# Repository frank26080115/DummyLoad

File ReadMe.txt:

Full project details at:

http://www.frank-zhao.com/dummyload/

The circuit and PCB are designed in EAGLE 6.3.0

Compiling the bootloader requires LUFA to be installed (not included, get it yourself)

The firmware is compiled using Atmel Studio 6.1, with the accompanying AVRToolChain, which has AVR GCC 4.7.2

The box is a Hammond Mfg RL6115

===================================

Instructions:

Build the circuit, the PCB and schematic are both provided, so it's up to you to find the parts and get the PCB made and then solder everything.

The box needs to be drilled and cut. I used a drill, a dremel, and some files to get this done.

After the circuit is built, use an AVR programmer to flash the bootloader into the ATmega32U4

To activate the bootloader, hold down the rotary encoder push button, and plug in the USB cable.

The bootloader behaves as a USBasp, use AVRDUDE to bootload the firmware.

Adjust the LCD contrast using the potentiometer.

The virtual USB serial port requires a driver, see http://www.pjrc.com/teensy/td_download.html and look for "Windows Serial Driver"

When you first use the dummy load, you must connect it to a computer and open up the virtual serial port to do the calibration.

===================================

Calibration:

This is a measurement tool. Because of the various errors and tolerances of the components being used, it needs to be calibrated before being useful. Calibration is done against a known "calibrated" power supply, which must have adjustable voltage, with both voltage and current readouts.

Make sure the virtual serial port is open in a serial terminal.

Connect the red plug to the black plug.

Type the command "calivolts:0" and press enter, wait until you see "voltageOffset" being shown.

Connect the dummy load to the power supply that was discussed previously.

Set the precision power supply to exactly 5V

Type the command "calivolts:5" and press enter, wait until you see "voltageScale" being shown. If you are not using 5V, you can type in another voltage.

Type the command "caliamps:0" and press enter, wait until you see "currentOffset" being shown.

Rotate the knob until the power supply says it is supplying exactly 500mA, then type the command "caliamps:500" and press enter, wait until you see "currentDacScale" and "currentAdcScale" being shown.

If you cannot get exactly 500mA, you can actually type in any number equal to the current being drawn.

All calibration values are stored in EEPROM. There are default values if the values are invalid or missing in the EEPROM.

====================================

Other Serial Terminal Commands

All of these commands are lower case, case sensitive, and must end with one of \r \n or \0, you can hit enter to do this.

"start" will start the logging output in comma separated value format

"stop" will stop the logging output

"single" will output only one line of measurement

"set:123.45" will set the current to 123.45 mA, you can specify any number you want

"set16:12345" will send 12345 to the DAC, this is only used for testing

"info" will report the calibration values

There are a few more internal testing commands that you do not need to know, see the source code if you are interested.

I recommend using RealTerm because it has a simple interface for logging to a file.

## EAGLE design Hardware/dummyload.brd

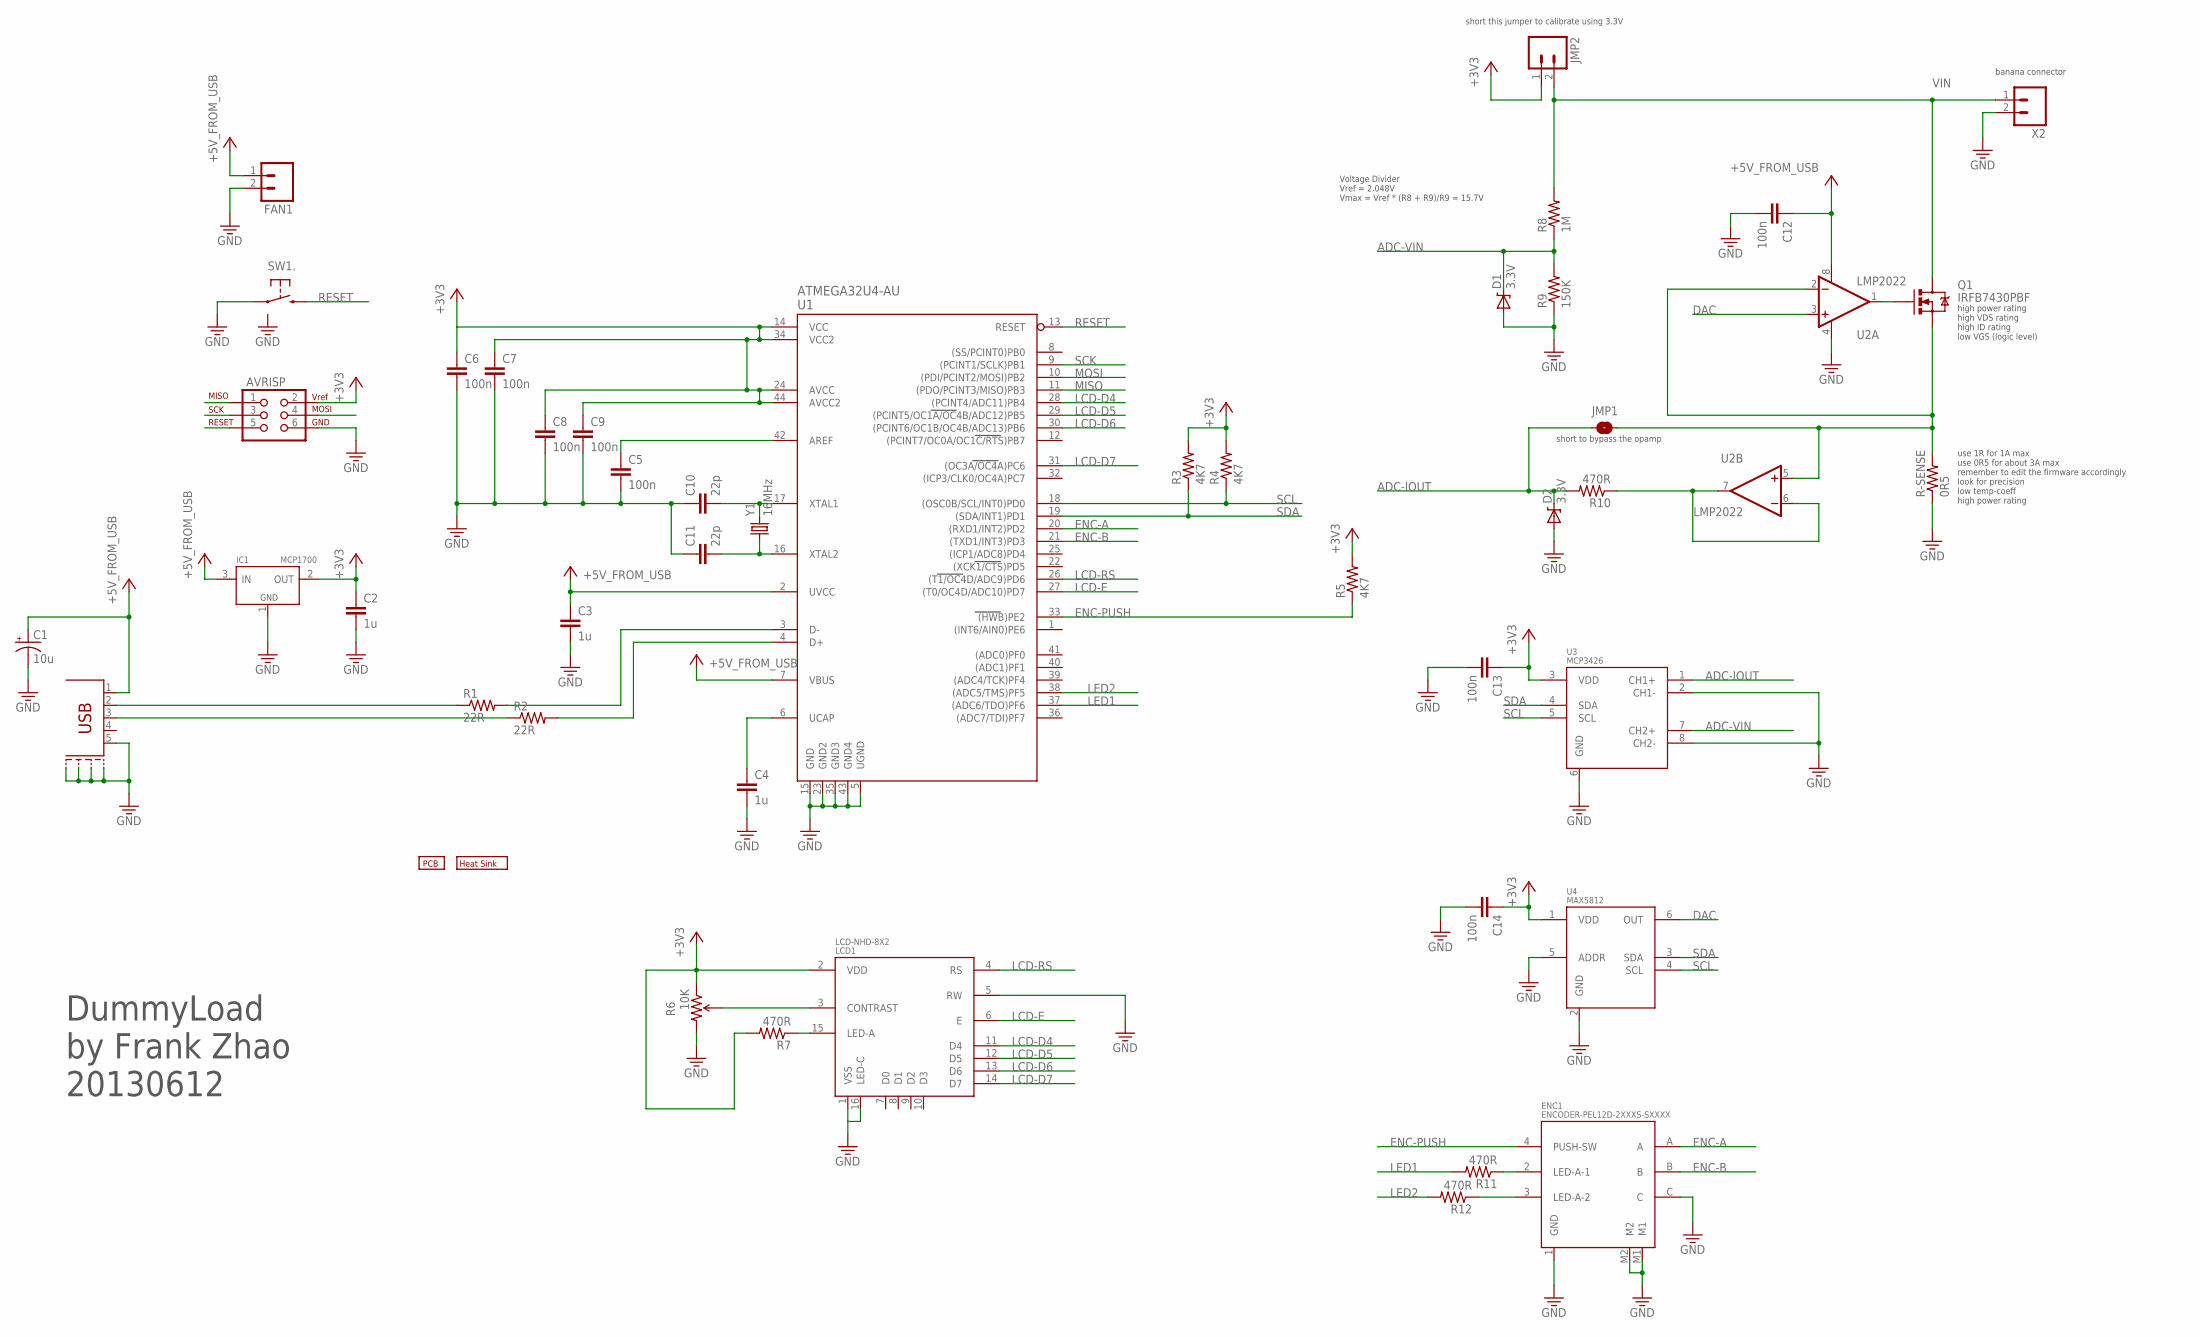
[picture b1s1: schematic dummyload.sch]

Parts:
AVRISP: AVR_SPI_PRG_62X3_LOCK; 2X3_LOCK
C1: 10u; EIA3216-KIT
C2, C3, C4: 1u; 0603-CAP
C5, C6, C7, C8, C9, C12, C13, C14: 100n; 0603-CAP
C10, C11: 22p; 0603-CAP
D1, D2: 3.3V; SOD-123
ENC1: ENCODER-PEL12D-2XXXS-SXXXX
FAN1: M02PTH; 1X02
IC1: MCP1700; SOT23-3
JMP1: SOLDERJUMPERNO; SJ_2S-NO
JMP2: M02-2MM; 1X02_2MM
LCD1: LCD-NHD-8X2; LCD-NHD-8X2-HEADER
Q1: IRFB7430PBF; TO220V
R1, R2: 22R; 0603-RES
R3, R4, R5: 4K7; 0603-RES
R6: 10K; TRIMPOT-3MM
R7, R10, R11, R12: 470R; 0603-RES
R8: 1M; 0603-RES
R9: 150K; 0603-RES
R-SENSE: 0R5; D2PACK
SW1: SWITCH-B3U-1110-BOSS; SWITCH-TACT-B3U-1100P-B
U1: ATMEGA32U4-AU; TQFP44
U2: LMP2022; MSOP-8
U3: MCP3426; MSOP-8
U4: MAX5812; SOT23-6
U$1: PCB-HAMMOND-RL6115
U$2: HEATSINK-TO220-VERT-42X25.4
X1: USB-MINI/MICRO-4S-4LEGS; USB_MICROB_4LEGS
X2: M025MM; SCREWTERMINAL-5MM-2
Y1: 16MHz; CRYSTAL-SMD-5X3

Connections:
+3V3: AVRISP.2, C2.1, C6.1, C7.1, C8.1, C9.1, C13.1, C14.1, IC1.2 (OUT), JMP2.1, LCD1.2 (VDD), R3.2, R4.2, R5.2, R6.1 (CCW), R7.2, U1.14 (VCC), U1.24 (AVCC), U1.34 (VCC2), U1.44 (AVCC2), U3.3 (VDD), U4.1 (VDD)
+5V_FROM_USB: C1.A (+), C3.1, C12.1, FAN1.1, IC1.3 (IN), U1.2 (UVCC), U1.7 (VBUS), U2.8 (V+), X1.1 (VBUS)
ADC-IOUT: D2.C, JMP1.1, R10.2, U3.1 (CH1+)
ADC-VIN: D1.C, R8.1, R9.2, U3.7 (CH2+)
DAC: U2.3 (+IN), U4.6 (OUT)
ENC-A: ENC1.A, U1.20 ((RXD1/INT2)PD2)
ENC-B: ENC1.B, U1.21 ((TXD1/INT3)PD3)
ENC-PUSH: ENC1.4 (PUSH-SW), R5.1, U1.33 ((HWB)PE2)
GND: AVRISP.6, C1.C (-), C2.2, C3.2, C4.2, C5.2, C6.2, C7.2, C8.2, C9.2, C10.1, C11.1, C12.2, C13.2, C14.2, D1.A, D2.A, ENC1.1 (GND), ENC1.C, ENC1.M1, ENC1.M2, FAN1.2, IC1.1 (GND), LCD1.1 (VSS), LCD1.5 (RW), LCD1.16 (LED-C), R6.3 (CW), R9.1, R-SENSE.1, SW1.1, SW1.BOSS, U1.5 (UGND), U1.15 (GND), U1.23 (GND2), U1.35 (GND3), U1.43 (GND4), U2.4 (V-), U3.2 (CH1-), U3.6 (GND), U3.8 (CH2-), U4.2 (GND), U4.5 (ADDR), X1.5 (GND), X1.P$3, X1.P$4, X1.P$7, X1.P$8, X2.2
LCD-D4: LCD1.11 (D4), U1.28 ((PCINT4/ADC11)PB4)
LCD-D5: LCD1.12 (D5), U1.29 ((PCINT5/OC1A/OC4B/ADC12)PB5)
LCD-D6: LCD1.13 (D6), U1.30 ((PCINT6/OC1B/OC4B/ADC13)PB6)
LCD-D7: LCD1.14 (D7), U1.31 ((OC3A/OC4A)PC6)
LCD-E: LCD1.6 (E), U1.27 ((T0/OC4D/ADC10)PD7)
LCD-RS: LCD1.4 (RS), U1.26 ((T1/OC4D/ADC9)PD6)
LED1: R11.2, U1.37 ((ADC6/TDO)PF6)
LED2: R12.2, U1.38 ((ADC5/TMS)PF5)
MISO: AVRISP.1, U1.11 ((PDO/PCINT3/MISO)PB3)
MOSI: AVRISP.4, U1.10 ((PDI/PCINT2/MOSI)PB2)
unnamed: C4.1, U1.6 (UCAP)
unnamed: LCD1.15 (LED-A), R7.1
unnamed: C10.2, U1.17 (XTAL1), Y1.3 (2)
unnamed: LCD1.3 (CONTRAST), R6.2 (WIPER)
unnamed: R1.1, X1.2 (DM)
unnamed: R2.1, X1.3 (DP)
unnamed: C11.2, U1.16 (XTAL2), Y1.1
unnamed: C5.1, U1.42 (AREF)
unnamed: JMP1.2, Q1.3 (S), R-SENSE.3 (2), U2.2 (-IN), U2.5 (+IN)
unnamed: R1.2, U1.3 (D-)
unnamed: R2.2, U1.4 (D+)
unnamed: R10.1, U2.6 (-IN), U2.7 (OUT)
unnamed: Q1.1 (G), U2.1 (OUT)
unnamed: ENC1.2 (LED-A-1), R11.1
unnamed: ENC1.3 (LED-A-2), R12.1
RESET: AVRISP.5, SW1.2, U1.13 (RESET)
SCK: AVRISP.3, U1.9 ((PCINT1/SCLK)PB1)
SCL: R4.1, U1.18 ((OSC0B/SCL/INT0)PD0), U3.5 (SCL), U4.4 (SCL)
SDA: R3.1, U1.19 ((SDA/INT1)PD1), U3.4 (SDA), U4.3 (SDA)
VIN: JMP2.2, Q1.2 (D), R8.2, X2.1

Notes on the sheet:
DummyLoad by Frank Zhao 20130612
Voltage Divider Vref = 2.048V Vmax = Vref * (R8 + R9)/R9 = 15.7V
short this jumper to calibrate using 3.3V
banana connector
use 1R for 1A max use 0R5 for about 3A max remember to edit the firmware accordingly look for precision low temp-coeff high power rating
short to bypass the opamp
high power rating high VDS rating high ID rating low VGS (logic level)

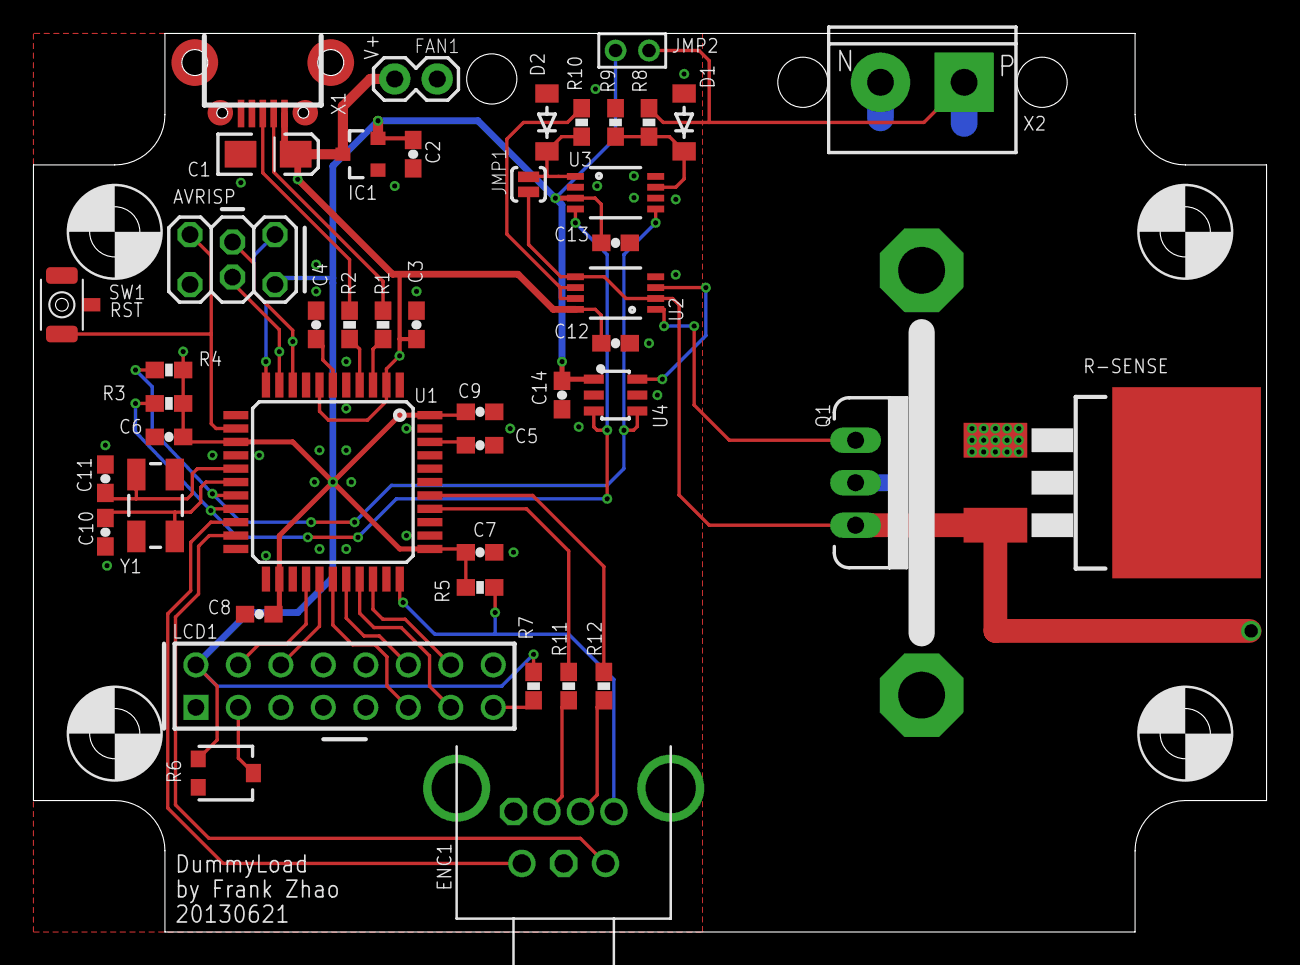
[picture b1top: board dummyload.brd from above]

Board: 2 copper layers, 73.7 x 53.7 mm, 47 parts (0 on the bottom side), 39 nets.

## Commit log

2013-06-21 first
2013-06-22 edited readme with some instructions
2013-06-22 got rid of "bad ckt fix"
2013-06-22 fixed bug, encoder will mess with log time
2013-06-22 updated to use 0.5 ohm cur sense resistor
2013-07-25 fixed timer, restored last DAC setting after cal, cal corrected using offsets
